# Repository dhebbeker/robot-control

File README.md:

This page describes the system developed.

Functions
=========

The robot system can be controlled by an operator through a web client.

There are two modes of operation.
One is a manual mode called "direct control".
The other is an automatic mode called "follow wall".

The commands are sent via a HTML form to the webserver hosted by the robot.
While a command is executed the controls are disabled.
The interaction between web client and webserver is achieved through responding to the form submission and periodic refreshes of the website.

direct control
--------------

These commands are available:

 - drive forward by 37,7mm
 - drive backward by 37,7mm
 - turn left by 86,4°
 - turn right by 86,4°

The numbers are crooked as they are a multiple of the distance of the way which can be measured with the motor encoder.

In direct control mode the trajectory which has been commanded to drive is recorded and displayed as a map.
The rendering of the map is not performed by the robot itself.
Instead the map data is send as part of the HTML page.
The page in turn queries another server capable of PHP to render the map using the provided data.
For this a small script is deployed on a server which uses the [GD library](https://www.php.net/manual/en/book.image.php).

If the robot's bumper are pushed (usually because the robot hits an obstacle) the robot stops immediately.
Only the drive backward command is effective in this case.

follow wall
-----------

In follow wall mode the robot follows a wall.
For this the distance sensors are used.

The algorithm first instructs the robot to turn around while sweeping its surrounding with the laser-ranging distance sensors.
Then it turns towards/outbound the closest distance, adjusts its distance to a fixed value and aligns itself to the wall.

It then repeatedly drives for a small distance while it measures the distance to the wall at the beginning and the end of this distance.
With this information it calculates the angle which it needs to turn in order to adjust its distance to the wall to the desired value within a certain distance.

> What is the direction to drive to in order to be at distance x after driving for y?

Then it turns to that direction and repeats the procedure.

In general the algorithm assumes that the wall is straight.
It tries to achieve the target distance to the wall.
Independent of whether the error is because the robot missed the target or because the wall actually was not straight.

The following sketch has been created with GeoGebra:

The sketch above shows how target vector the the distance to the wall "t" is calculated.

 1. The robot starts a position P1 and measures the distance to the wall "c".
 2. The robot drives for a defined distance "d" to the next point P2.
 3. The distance to the wall "f" is measured. f=c+b
 4. Using trigonometric functions the target vector is calculated.

Hardware Setup
==============

components
----------

The main components of the system are:

 - Robot System Robby RP5 ROBOT (CCRP5) which contains (among other things):
    - chain drive with 2 motors
    - optical motor encoder made of simple light barriers
 - NodeMCU version 3
 - 4× distance sensor: Time-of-Flight (ToF), laser-ranging, miniature sensor by STMicroelectronics [VL53L1](https://www.st.com/en/imaging-and-photonics-solutions/vl53l1.html)
 - a bumper made of LEGO Mindstorms (first generation) parts with 2 micro-switches

### robot base CCRP5

The robot base is the "Robot System Robby RP5 ROBOT (CCRP5)" by Conrad Electronic GmbH. It is a mobile robot with chain drive. Its main processor is a C-Control/BASIC microcomputer. It was originally distributed under the order code `19 03 33`, EAN: `4016138222968`.

Resources:

 - [product website](https://www.conrad.de/de/p/roboter-robby-rp5-190333.html) with firmware, manuals, schematics and more for download
 - [Wiki article at RN-Wissen.de](https://rn-wissen.de/wiki/index.php/CCRP5) with detailed description of the circuits

As copyright or other restrictions may apply to the resources, I will not distribute them. I can only hope they will remain available.

### NodeMCU

NodeMCU is a simple board. Its main component is a ESP8266 system on a chip. It contains a Wi-Fi microchip with microcontroller capability. This simplifies to develop programs which can easily connect to the internet.

It can easily be programmed with the Arduino IDE. Board support packages for NodeMCU are available.

system design
-------------

The CCRP5 has two microcontrollers:

 - subsystem IC2 `MC68HC705KJ1`
 - main controller IC7 `MC68HC05B6`

The CCRP5 is designed such as, the subsystem is only programmed by the manufacturer. There is no in-system programming interface. All applications shall be written for the main controller.

The main controller should be programmed with a proprietary development environment CCEW32D. Programs must be written in CCBASIC, which is a dialect of the BASIC programming language. The applications are based on a firmware `P5DRIV.S19`. CCBASIC is a low level language. The documentation is available to a limited extent.

This projects aims to control the hardware of the CCRP5 without the CCRP5 microcontrollers.
Thus an additional "piggyback" PCBA is installed onto the basis CCRP5 PCBA which is tapping into the signals from the CCRP5.
The piggyback PCBA includes the NodeMCU board.

connections
-----------

### Piggyback PCBA

The schematics of the piggyback PCBA are described in `hardware/robot-control-circuit/robot-control-circuit.sch`.

### Basis PCBA

The original schematics can be retrieved at the above mentioned resources.

Some modifications were made to the CCRP5's PCBA.
The signals `D/A 1` and `D/A 2` have been disconnected from the pins of the CCRP5's main microcontroller (IC7) because the pins are configured as drain (referencing to CCRP5's schematics).
This interferes with the control of the NodeMCU and causes an 80mA current.
The signals have been disconnected by un-soldering and lifting of the microcontroller's pins.

Also the IO-expander `I11` has been disconnected in order to be able to control the current for the IR-LEDs `D3` and `D4`.

Software
========

The source code is written in C++.
It is compiled and programmed with the [Arduino IDE][].

Dependencies:

 - [Arduino IDE][]. Tested with v2.0.0-beta.4 should work with 1.5.x+.
 - The [board support package for the ESP8266 chip](https://github.com/esp8266/Arduino) must be installed.
   Tested using version 2.7.4.
   Version 3.0.0, (3.0.1 not tested) and 3.0.2 do not work because of [this bug](https://github.com/espressif/esp-idf/issues/4542).
 - The [Arduino library VL53L1 by STM32duino](https://github.com/stm32duino/VL53L1) must be installed. Tested using version 2.0.1.
 - The [SimplyAtomic library](https://github.com/wizard97/SimplyAtomic) must be installed. Tested in version 1.0.
 - The [MPC23017 library by Bertrand Lemasle](https://github.com/blemasle/arduino-mcp23017) must be installed. Tested in version 2.0.0.

[Arduino IDE]: https://www.arduino.cc/en/Main/Software

Developing without Arduino IDE
------------------------------

In case one wants to use an IDE other than Arduino to write the code some provisions should be met:

 - Add the following include paths
   (where `${ARDUINO_LIB_PATH}` is the path to the Arduino libraries (for example `~/Arduino/libraries`),
          `${AVR_PATH}` is the path to the AVR header files (for example `~/.arduino15/packages/arduino/tools/avr-gcc/7.3.0-atmel3.6.1-arduino7/avr/include`),
          `${ESP8266_HARDWARE_PATH}` is the path to the hardware part of the ESP8266 board support package (for example `~/.arduino15/packages/esp8266/hardware/esp8266/2.7.4`),
          `${ESP8266_COMPILER_PATH}` is the path to the software part of the ESP8266 board support package (for example `~/.arduino15/packages/esp8266/tools/xtensa-lx106-elf-gcc/2.5.0-4-b40a506`)):
   - `${AVR_PATH}`
   - `${ARDUINO_LIB_PATH}/MCP23017/src`
   - `${ARDUINO_LIB_PATH}/SimplyAtomic`
   - `${ARDUINO_LIB_PATH}/STM32duino_VL53L1/src`
   - `${ESP8266_HARDWARE_PATH}/cores/esp8266`
   - `${ESP8266_HARDWARE_PATH}/tools/sdk/include`
   - `${ESP8266_HARDWARE_PATH}/tools/sdk/lwip2/include`
   - `${ESP8266_HARDWARE_PATH}/variants/nodemcu`
   - `${ESP8266_HARDWARE_PATH}/libraries/Wire`
   - `${ESP8266_HARDWARE_PATH}/libraries/ESP8266WiFi/src`
   - `${ESP8266_HARDWARE_PATH}/libraries/ESP8266WebServer/src`
   - `${ESP8266_COMPILER_PATH}/lib/gcc/xtensa-lx106-elf/4.8.2/include`
   - `${ESP8266_COMPILER_PATH}/xtensa-lx106-elf/include`
   - `${ESP8266_COMPILER_PATH}/xtensa-lx106-elf/include/c++/4.8.2`
 - Add the following preprocessor macros:
   - `ARDUINO_ARCH_ESP8266`

For compiling and flashing the Arduino IDE is recommended.

Configuration
-------------

In order to reduce dynamic memory usage, one may reduce the maximum number of range data produced by the VL53L1 library.
In order to achive that, add the following line to the [`platform.local.txt`](https://arduino.github.io/arduino-cli/0.20/platform-specification/#platformlocaltxt) file.
That file must be in `${ESP8266_HARDWARE_PATH}`.
Create it if not existent.

    compiler.cpp.extra_flags=-DVL53L1_MAX_RANGE_RESULTS=1

This defines a predefined macro which sets the number of maximum range data to 1.

Issues
======

Distance measurement depends on orientation
-------------------------------------------

A major issue with the system design is, that the shortest distance measured to another object depends considerably on the orientation of the robot to that object.
This is due to the fact that the distance is measured at fixed directions with a tight beam.
The robot measures the distance at some angles.
The measurement is done with a tight beam and does not take into account variations within a circular sector.

The result is, that in order to determine the shortest distance to an object, the robot must rotate such that a full sweep around the robot is performed.

This also has the following effect.
If the robot tries to align to a straight wall, it will turn in order to adjust its distance to the wall.
Turning will result in a changed perceived distance to the straight wall.

For example in case the robot is aligned to the wall but the distance is too short.
The robot will turn away from the wall in order to increase its actual distance to the wall.
By turning away (pure rotation) from the wall the sensor which was previously directed to the wall (parallel to the normal vector) will now light the wall with a non-right angle.
Thus the measured distance by that sensor will increase.
Even though the actual distance did not really increase.

This effect could be counted back only if the shape of the object is known (for example a straight wall).
But usually the shape of the object is unknown.

This effects complicates the task to follow the shape of objects.
Especially using a simple PID controller.

Coarse odometry sensor
----------------------

Movements of the robot (driving, turning, rotation) are performed in increments which are captured by an optical light barrier.
That light barrier is triggered when a cog in the transmission of the drives is at certain angles.
Using the information of the direction in which a motor turns, this information is used to calculate the movement of the robot.

Conversely movements of the robot must be in full increments of the slots in the cog.
As the transmission of that cog to the ground is not very high, or the slots are too distant, the minimum distance driven by one chain drive in one increment (distance between slots) is approximately 38mm.

Movements by multiples of such big increments makes the control of the robot position difficult.
Especially as the robot can not adjust its orientation by small angles.

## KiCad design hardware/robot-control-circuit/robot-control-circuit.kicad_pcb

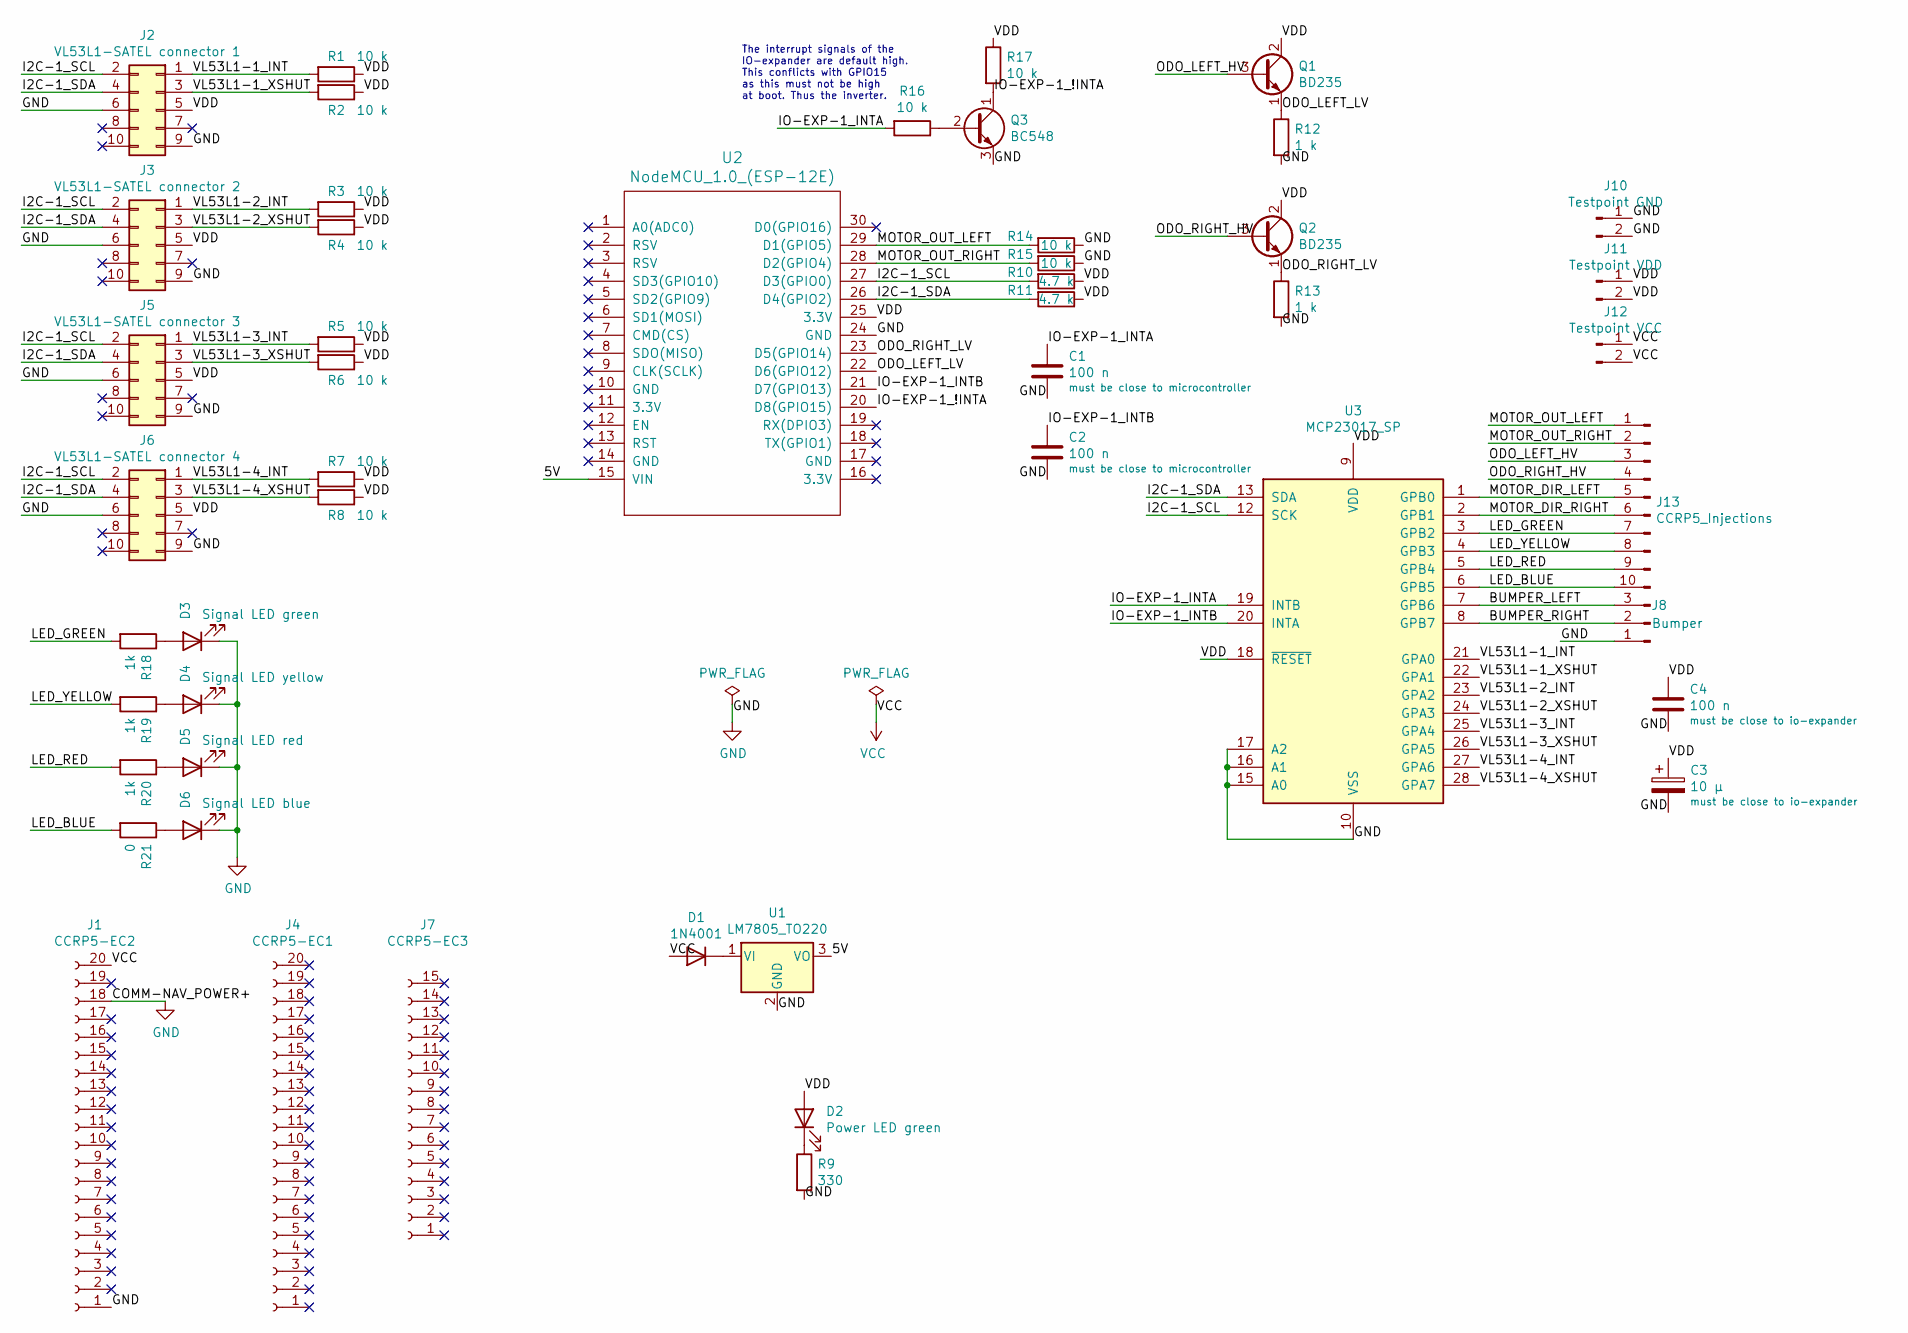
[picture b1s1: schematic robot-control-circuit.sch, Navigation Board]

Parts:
C1, C2, C4: 100 n; C_Rect_L4.6mm_W2.0mm_P2.50mm_MKS02_FKP02
C3: 10 µ; CP_Radial_D5.0mm_P2.50mm
D1: 1N4001; D_DO-34_SOD68_P2.54mm_Vertical_KathodeUp
D2: Power LED green; LED_D3.0mm
D3: Signal LED green; LED_D3.0mm
D4: Signal LED yellow; LED_D3.0mm
D5: Signal LED red; LED_D3.0mm
D6: Signal LED blue; LED_D3.0mm
J1: CCRP5-EC2; PinHeader_1x20_P2.54mm_Vertical; Part SSA-120-W-T
J2: VL53L1-SATEL connector 1; PinSocket_2x05_P2.54mm_Horizontal
J3: VL53L1-SATEL connector 2; PinSocket_2x05_P2.54mm_Horizontal
J4: CCRP5-EC1; PinHeader_1x20_P2.54mm_Vertical; Part SSA-120-W-T
J5: VL53L1-SATEL connector 3; PinSocket_2x05_P2.54mm_Horizontal
J6: VL53L1-SATEL connector 4; PinSocket_2x05_P2.54mm_Horizontal
J7: CCRP5-EC3; PinHeader_1x15_P2.54mm_Vertical
J8: Bumper; PinHeader_1x03_P2.54mm_Vertical
J10: Testpoint GND; PinHeader_1x02_P2.54mm_Vertical
J11: Testpoint VDD; PinHeader_1x02_P2.54mm_Vertical
J12: Testpoint VCC; PinHeader_1x02_P2.54mm_Vertical
J13: CCRP5_Injections; PinHeader_1x10_P2.54mm_Vertical
Q1, Q2: BD235; TO-126-3_Vertical
Q3: BC548; TO-92_Inline_Wide
R1, R2, R3, R4, R5, R6, R7, R8, R14, R15, R16, R17: 10 k; R_Axial_DIN0204_L3.6mm_D1.6mm_P2.54mm_Vertical
R9: 330; R_Axial_DIN0204_L3.6mm_D1.6mm_P2.54mm_Vertical
R10, R11: 4.7 k; R_Axial_DIN0204_L3.6mm_D1.6mm_P2.54mm_Vertical
R12, R13: 1 k; R_Axial_DIN0204_L3.6mm_D1.6mm_P2.54mm_Vertical
R18, R19, R20: 1k; R_Axial_DIN0204_L3.6mm_D1.6mm_P2.54mm_Vertical
R21: 0; R_Axial_DIN0204_L3.6mm_D1.6mm_P2.54mm_Vertical
U1: LM7805_TO220; TO-220-3_Vertical
U2: NodeMCU_1.0_(ESP-12E); NodeMCU1.0(12-E)
U3: MCP23017_SP; DIP-28_W7.62mm

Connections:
/5V: U1.3 (VO), U2.15 (VIN)
/BUMPER_LEFT: J8.3, U3.7 (GPB6)
/BUMPER_RIGHT: J8.2, U3.8 (GPB7)
/I2C-1_SCL: J2.2, J3.2, J5.2, J6.2, R10.2, U2.27 (D3(GPIO0)), U3.12 (SCK)
/I2C-1_SDA: J2.4, J3.4, J5.4, J6.4, R11.2, U2.26 (D4(GPIO2)), U3.13 (SDA)
/IO-EXP-1_!INTA: Q3.1 (C), R17.2, U2.20 (D8(GPIO15))
/IO-EXP-1_INTA: C1.1, R16.2, U3.19 (INTB)
/IO-EXP-1_INTB: C2.1, U2.21 (D7(GPIO13)), U3.20 (INTA)
/LED_BLUE: J13.10, R21.2, U3.6 (GPB5)
/LED_GREEN: J13.7, R18.2, U3.3 (GPB2)
/LED_RED: J13.9, R20.2, U3.5 (GPB4)
/LED_YELLOW: J13.8, R19.2, U3.4 (GPB3)
/MOTOR_DIR_LEFT: J13.5, U3.1 (GPB0)
/MOTOR_DIR_RIGHT: J13.6, U3.2 (GPB1)
/MOTOR_OUT_LEFT: J13.1, R14.2, U2.29 (D1(GPIO5))
/MOTOR_OUT_RIGHT: J13.2, R15.2, U2.28 (D2(GPIO4))
/ODO_LEFT_HV: J13.3, Q1.3 (B)
/ODO_LEFT_LV: Q1.1 (E), R12.1, U2.22 (D6(GPIO12))
/ODO_RIGHT_HV: J13.4, Q2.3 (B)
/ODO_RIGHT_LV: Q2.1 (E), R13.1, U2.23 (D5(GPIO14))
/VDD: C3.1, C4.1, D2.2 (A), J2.5, J3.5, J5.5, J6.5, J11.1, J11.2, Q1.2 (C), Q2.2 (C), R1.1, R2.1, R3.1, R4.1, R5.1, R6.1, R7.1, R8.1, R10.1, R11.1, R17.1, U2.25 (3.3V), U3.9 (VDD), U3.18 (~RESET~)
/VL53L1-1_INT: J2.1, R1.2, U3.21 (GPA0)
/VL53L1-1_XSHUT: J2.3, R2.2, U3.22 (GPA1)
/VL53L1-2_INT: J3.1, R3.2, U3.23 (GPA2)
/VL53L1-2_XSHUT: J3.3, R4.2, U3.24 (GPA3)
/VL53L1-3_INT: J5.1, R5.2, U3.25 (GPA4)
/VL53L1-3_XSHUT: J5.3, R6.2, U3.26 (GPA5)
/VL53L1-4_INT: J6.1, R7.2, U3.27 (GPA6)
/VL53L1-4_XSHUT: J6.3, R8.2, U3.28 (GPA7)
GND: C1.2, C2.2, C3.2, C4.2, D3.1 (K), D4.1 (K), D5.1 (K), D6.1 (K), J1.1, J1.18, J2.6, J2.9, J3.6, J3.9, J5.6, J5.9, J6.6, J6.9, J8.1, J10.1, J10.2, Q3.3 (E), R9.2, R12.2, R13.2, R14.1, R15.1, U1.2 (GND), U2.24 (GND), U3.10 (VSS), U3.15 (A0), U3.16 (A1), U3.17 (A2)
unnamed: D1.1 (K), U1.1 (VI)
unnamed: D2.1 (K), R9.1
unnamed: D3.2 (A), R18.1
unnamed: D4.2 (A), R19.1
unnamed: D5.2 (A), R20.1
unnamed: D6.2 (A), R21.1
unnamed: Q3.2 (B), R16.1
VCC: D1.2 (A), J1.20, J12.1, J12.2

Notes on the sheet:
The interrupt signals of the IO-expander are default high. This conflicts with GPIO15 as this must not be high at boot. Thus the inverter.

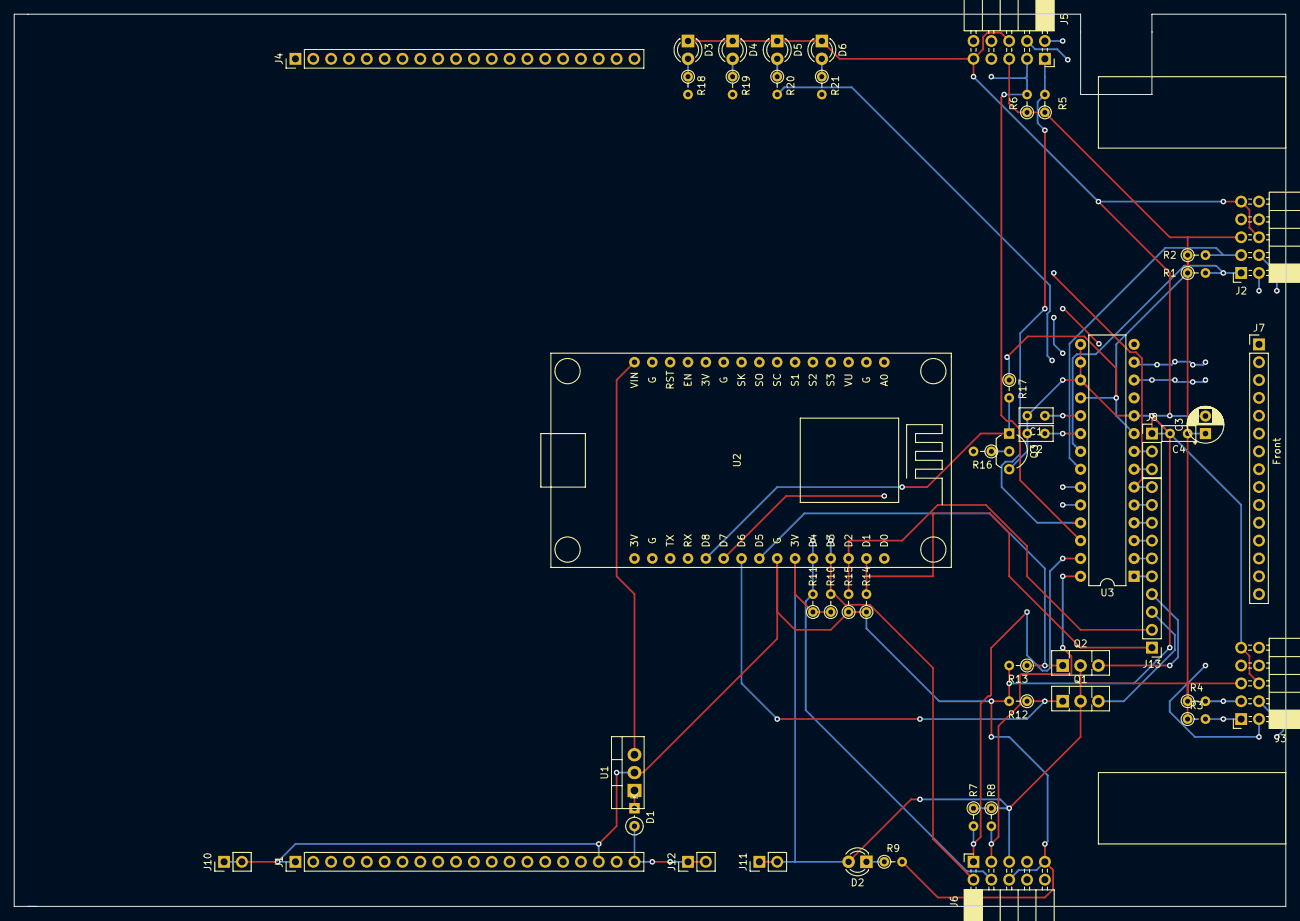
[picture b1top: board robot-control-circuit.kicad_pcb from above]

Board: 4 copper layers, 181.0 x 127.0 mm, 49 parts (0 on the bottom side), 38 nets.

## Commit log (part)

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2021-01-17 start
2021-01-17 Add current work in progress.
    I have been working on this project for a couple of days since 2021-01-07.
2021-01-17 Added some basic documentation on the hardware.
2021-01-17 Added a little documentation on the source code.
2021-01-17 Added source code and documentation used to calibrate drives.
2021-01-17 Moved source code to dedicated source directory.
2021-02-14 Add pinout table for ESP8266.
    Copied from https://randomnerdtutorials.com/esp8266-pinout-reference-gpios/#table
2021-04-25 Define circuit and PCB.
    Includes
    - 1 NodeMCU
    - 4 VL53C1CB breakout boards
    - 1 MCP23017 IO expander
    - 2 front bumper
2021-04-25 Add workaround for bug in external board package.
    See https://github.com/esp8266/Arduino/issues/5787#issuecomment-465852231
    Beware: The #undef directive must be issued after `#include <Arduino.h>` and before including any file that defines `std::round`.
2021-05-02 Added capacitors for io-expander.
2021-05-02 Directly connect !RESET of IO-expander to VDD and invert INTA.
2021-05-04 Corrected left right bumper signal labels.
2021-05-04 Added function to attach interrupts to digital pin.
    Tested successfully!
2021-05-04 Change interface for virtual pin to integers.
    In order to be compatible with Arduino.
2021-05-04 Add interface for GPIO and pin implementation.
2021-05-04 Add PWM function to DigitalPin.
2021-05-04 Add overload for digitalPinToInterrupt() and analogWrite().
2021-05-05 Added IO expander.
2021-05-05 Adjust Drive such that it takes pins as runtime objects instead of template arguments.
2021-05-05 Set correct I2C address for IO expander.
2021-05-05 Add initialization of I2C for dedicated pins.
2021-05-05 Sort #include order.
2021-05-05 Initialize remaining board pins.
2021-05-05 Use macro for PI, as std::acos is not constexpr.
2021-05-06 Add stop function.
2021-05-08 Use same type as in declaration.
2021-05-09 Added documentation on odometry calculation.
    See https://rn-wissen.de/wiki/index.php/CCRP5#Odometrie
2021-05-09 Add constant odoMinIntervalDuration.
2021-05-09 Added threshold to odometry counter.
    In order to suppress bouncing.
2021-05-09 Attach bumper interrupt to stop condition.
2021-05-10 Added PHP script to plot a random route.
2021-05-11 Calculate position and display it.
2021-05-11 Added backward direction for position calculation.
2021-05-11 Add size() function to get size of arrays.
    Source: https://en.cppreference.com/w/cpp/iterator/size
2021-05-11 Added position plot to HTML.
    HTML source is now rendered in background using buffering.
2021-05-11 Added automatic refresh.
    HTML source is converted to C/C++ string using this online converter: https://tomeko.net/online_tools/cpp_text_escape.php
2021-05-11 Added lock to move but backwards in case bumper is pressed.
2021-05-19 Added patterns to .gitignore.
2021-05-19 Use public URI for kicad-ESP8266 submodule.
2021-05-23 Rename DigitalPin.hpp.
2021-05-23 Document GpioInterface and GpioPin.
2021-05-23 Add child class to VL53L1 which accepts GpioInterface.
2021-07-01 Outsourced code.
2021-07-14 Minor adjustments.
2021-09-08 Add virgin doxygen configuration file.
2021-09-08 Add ideas for software architecture.
2021-09-08 Add include directories to doxygen documentation.
2021-09-08 Add snapshot on directory structure before establishing software layers.
2021-10-09 Moved files for better software structure.
2021-10-10 Moved files to src/ directory for recursive build.
    See https://github.com/arduino/arduino-builder/pull/148
2021-10-10 Update doxygen configuration to version 1.9.3.
    - Automatic update with `doxygen -u`.
    - Added extension mapping for `ino` files (Arduino Sketches)
    - Added path for mainpage
2021-10-10 Adjusted ignore to new directory structure.
2021-10-10 Adjusted include paths.
2021-10-10 Move definition of PI to separate file.
    See https://en.cppreference.com/w/cpp/header/numbers
2021-10-10 Adjust include paths.
2021-10-10 Moved content of sketch (INO) to main.cpp.
    Because the file with proper C++ file extension is easier to evaluate by other IDEs.
2021-10-10 Misc.
2021-10-10 Added the libraries used as git submodules for convenience.
2021-10-22 Reduced doxygen configuration to essentials.
2021-10-23 Added prototype for circular buffer.
2021-10-23 Added helper-type for minimum sized integer type.
    Copied from https://stackoverflow.com/a/41838047/ and adapted.
2021-10-23 Fixed circular buffer and applied dynamic size_type.
2021-10-23 Add function which does calculate the mean value of all elements of a container.
2021-10-24 Added clear() to circular_buffer.
2021-10-24 Add introduction to main documentation.
    This guides doxygen not to use the first header as title.
2021-10-24 Added documentation of necessary include paths and preprocessor macros.
2021-10-24 Enhance report for range measuring.
2021-10-24 Change sensor report to single range.
2021-10-24 Change sensor report to store sensor distance.
2021-10-24 Add function to steer drives with independent speed.
2021-10-24 Rotate in case no wall is seen.
2021-10-29 Update ESP8266 board support package.
2021-10-29 Renamed template parameter as the compiler did not like it.
    ¯\_(ツ)_/¯
2021-10-29 Change rotate function to use the signedness of the angle to determine the direction.
2021-10-29 Changed wall algorithm to measure and turn an angle.
2021-10-30 Instruct the user to use ESP8266 board support package version 2.7.4 (downgrade).
    Because of issue with compiler.
    See
    - https://github.com/espressif/esp-idf/issues/4542
    - https://gcc.gnu.org/bugzilla/show_bug.cgi?id=70435
2021-10-30 Add debug output.
2021-10-30 Use float literals for divisions.
2021-10-30 Add empty else path for documentation.
2021-10-30 Add safety not to attempt to turn for 0 steps.
    As this may still lead to turning because the stop is only triggered after the sensor is triggered.
2021-10-30 Fix error in calculation of angle.
2021-11-01 Add macro for a polling wait.
2021-11-01 Fix problem with negative rotation.
2021-11-06 Move isBumperPressed() to board.
2021-11-06 Move stepsPerDeg to header as it will be used by other files.
2021-11-06 Begin to write a state machine for bearing functionality.
2021-11-06 Add missing namespace prefix.
2021-11-06 Fix non-static constexpr member.
2021-11-06 Refactoring board.
    Hide pins and other hardware as good as possible within the scope of board.
2021-11-06 Implement scanning for blip.
2021-11-07 Add calibration function.
2021-11-07 Move workaround for Arduino defined macros to header.
2021-11-07 Improve serial communication output.
2021-11-07 Work on aligning to wall.
2021-11-07 Re-measured rotation.
2021-11-07 Fix calculation of vector to blip.
2021-11-08 Added LEDs for generic signaling purposes.
2021-11-17 Connected new LEDs.
2021-11-28 Automatic formatting.
2021-11-28 Add function to interact with human via serial interface.
2021-12-05 Added debug LEDs.
2021-12-05 Change white debug led.
2021-12-05 Add initial test for distance sensors.
2021-12-12 Added angle calculation for following wall.
2022-01-06 Add documentation to AligningToWall::operation()
2022-01-06 Create generic class for state machines.
2022-01-06 Apply PollingStateMachine to Bearing class.
2022-01-06 Refine PollingStateMachine
2022-01-06 Create sub-state-machine for following wall.
2022-01-06 Added algorithm to drive along the wall.
2022-01-07 Debugging and enhance wall following algorithm.
2022-01-08 Add function to retrieve a specific sensor or an error.
2022-01-08 Added submodules for remote debug connection.
2022-01-08 Defined interface for debugging via Serial and WiFi.
2022-01-09 Added documentation.
2022-01-09 Use dedicated macro to enable debugging via serial.
    Because with DEBUG_ESP_PORT there were frequent random crashes.
2022-01-09 Remove debugging demo.
2022-01-09 Rename SERIAL macro to avoid conflicts.
2022-01-09 Added configuration feature to VL53L1 library.
2022-01-09 Add instructions on how to configure VL53L1 library.
2022-01-09 Use automatic calculation of sensor numbers.
2022-01-09 Reduce the number of used distance sensor structures.
2022-01-09 Adjust debug message outputs.
2022-01-09 Add delay in state machine in order to simplify debugging.
    This shall be temporary!
2022-02-04 Update STM32duino_VL53L1 library to 2.1.0.
2022-02-19 Fix illegal constexpr.
    implicit use of 'this' pointer is only allowed within the evaluation of a call to a 'constexpr' member function
2022-02-19 Replace call to non-constexpr function by constexpr literal.
    The previous code was non-standard conform.
2022-02-20 Add file and line to debug output.
2022-02-20 [WIP] Debugging.
2022-02-21 Move check for operateOnRightWall in seperate function.
2022-02-27 Replace ° by degrees.
    As symbol is not properly shown on serial terminal.
2022-03-13 Make test for distance sensores available to main().
2022-03-14 Potential fix.
2022-05-07 Add documentation.
2022-05-07 Drives: Only evaluate intervall in case the drive is not supposed to be idle.
2022-05-07 Correct format of printf of unsigned long.
2022-05-07 Calibrate rotation.
2022-05-07 Remove obsolete variables.
2022-05-08 Added macro for "safe new".
2022-05-08 Changed sensor from front-right to front-left.
2022-05-08 Use new_s and new_s_pre for debugging.
2022-05-08 Add yield() in order to avoid "Soft WDT reset".
2022-05-08 Round values to int.
2022-05-11 Removed waiting which was for debugging.
2022-05-12 Removed debugging via WiFi (RemoteDebug).
    This has not been used and I would like to use the webserver for other purposes.
2022-05-12 Re-added webserver.
    This reverts commit 8979a3042e51abb840871faab4e669606a54a4cd.
2022-05-12 [WIP] Make old code compileable again.
2022-05-15 Added helper function for constexpr max().
    This is necessary as:
    - C++11 is used and there max() is not declared constexpr
    - C++11 is used because the compiler version supporting C++14 has a bug (see https://github.com/espressif/esp-idf/issues/4542)
    - function must be declared in a namespace, as Arduino.h declares std::max in global namespace 😠 https://github.com/esp8266/Arduino/commit/dfcaa1b85464f16156d0920dd6ddff5697ac13dc#diff-3d1fc8ffad5bc4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
    - code copied from https://en.cppreference.com/w/cpp/algorithm/max#Possible_implementation
2022-05-15 Added button on website to control function "follow wall".
2022-05-15 Add mechanism to set the next state of a state machine.
2022-05-15 Add possibilities to start and stop bearing activity.
2022-05-15 Manage different activities by webserver.
2022-05-15 Trigger application activities.
2022-05-15 Increase refresh rate.
2022-05-19 Complete documentation.
2022-05-19 Add MIT license for my work.
2022-05-19 Added workflow for doxygen documentation generation.
    Copied from https://github.com/satu0king/Github-Documentation-With-Doxygen/commit/67a22827637fcb932f9009696d280c2699417719
2022-05-19 deploy: fe7f552e7d9aa4ae2bb43b58ef45d780effe1095
2022-05-19 Round distances to multiples of the odometry intervall.
    Because else, the algorithm assumes that distances are driven which can actually not be achieved.
2022-05-22 Prepare for new control algorithm.
2022-05-22 Add some notes.
2022-05-25 Move PID library.
2022-05-25 Use PID controller.
2022-05-25 Add exception handling for the case that the robot points to the wall.
2022-06-01 Do not accept NAN as target angle.
2022-06-01 Avoid that the dividend is greater than the divisor.
    As this results to an invalid argument to acos().
2022-06-11 Use for distance sensor a structure composed of the sensor interface and the angle the sensor directs to.
2022-07-04 Add documentation for calculation.
2022-07-04 Add debug message.
2022-07-25 Add sections for issues.
2022-07-25 Describe issue with tight beam distance measuring.
2022-07-25 Describe issue with coarse odometry sensor.
